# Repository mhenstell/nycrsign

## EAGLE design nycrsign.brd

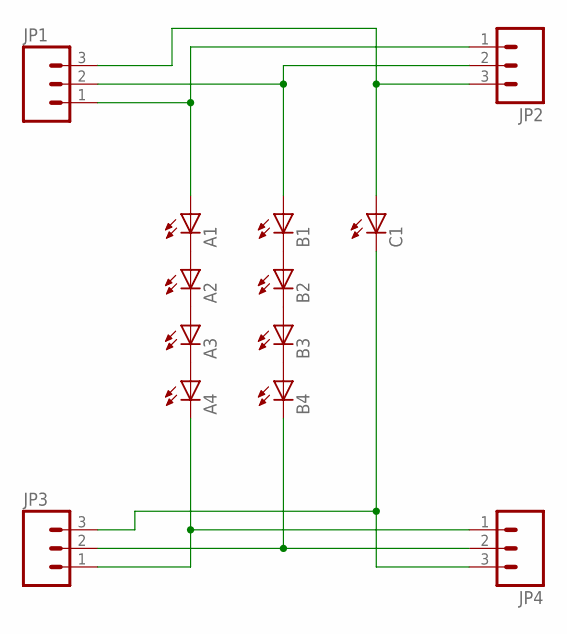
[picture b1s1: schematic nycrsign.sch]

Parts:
A1, A2, A3, A4: LED5MM
B1, B2, B3, B4: LED5MM
C1: LED5MM
JP1, JP2, JP3, JP4: M03LONGPADS; 1X03_LONGPADS

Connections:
A4: A4.K (C), JP3.1, JP4.1
unnamed: A1.K (C), A2.A
unnamed: A2.K (C), A3.A
unnamed: A3.K (C), A4.A
unnamed: B1.K (C), B2.A
unnamed: B2.K (C), B3.A
unnamed: B3.K (C), B4.A
unnamed: A1.A, JP1.1, JP2.1
unnamed: B1.A, JP1.2, JP2.2
unnamed: C1.A, JP1.3, JP2.3
unnamed: B4.K (C), JP3.2, JP4.2
unnamed: C1.K (C), JP3.3, JP4.3

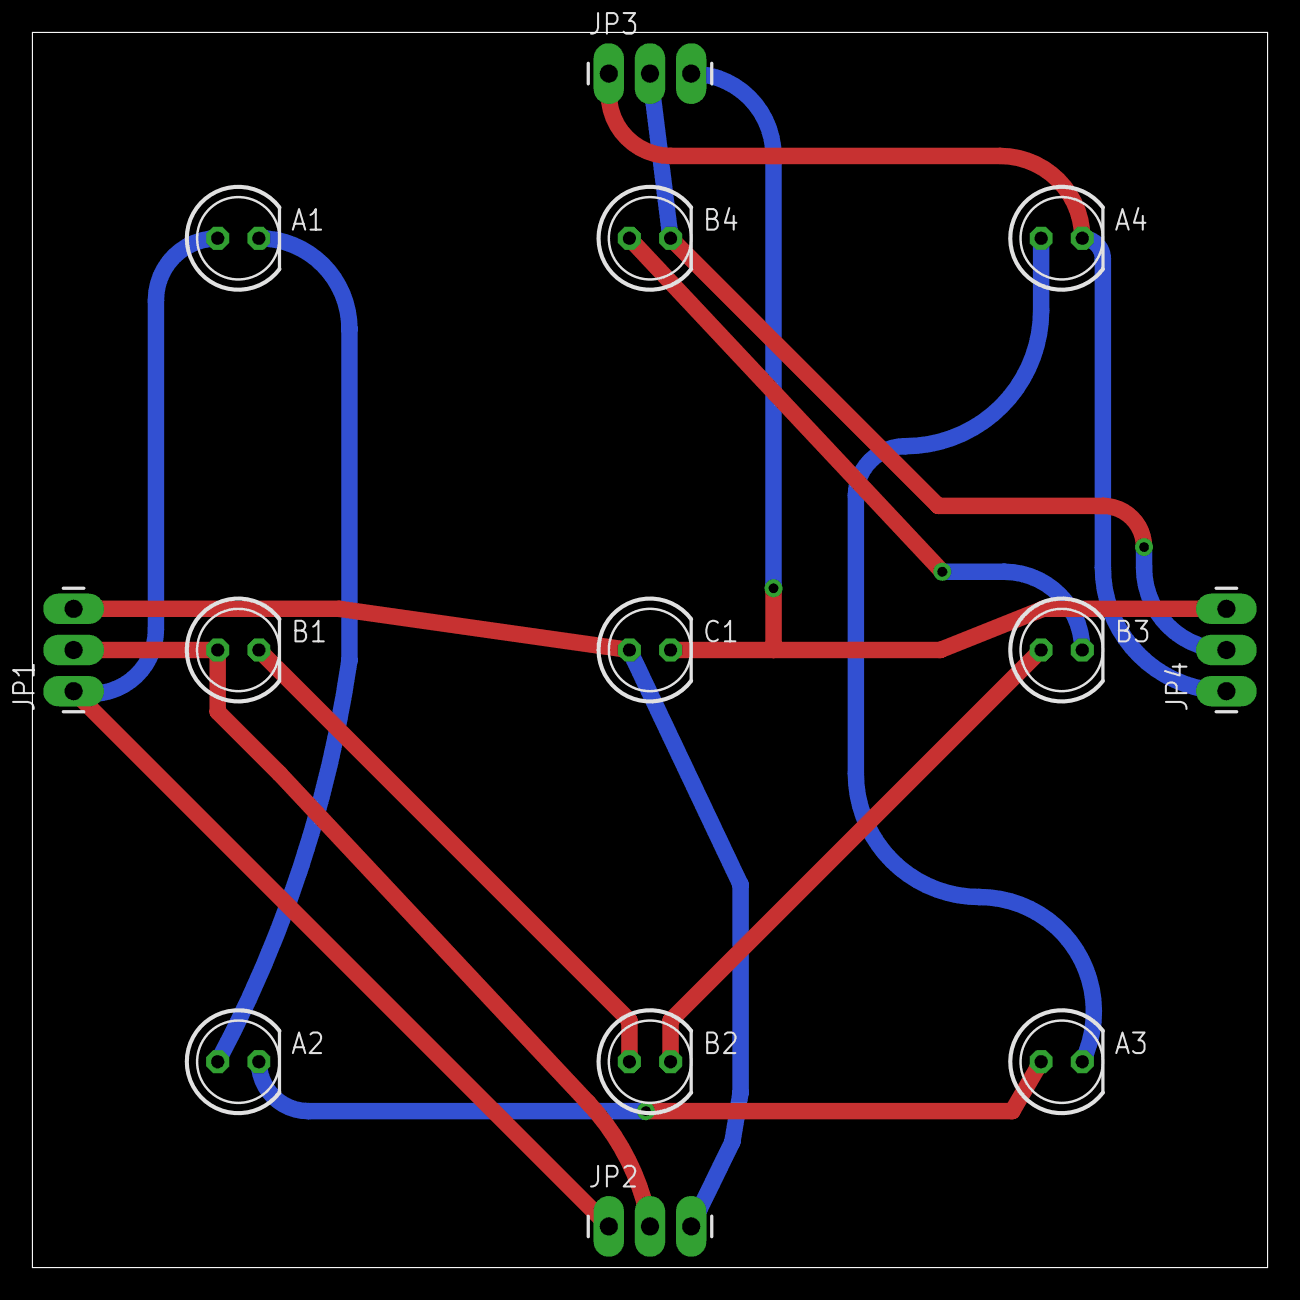
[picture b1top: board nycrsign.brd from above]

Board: 2 copper layers, 76.2 x 76.2 mm, 13 parts (0 on the bottom side), 12 nets.

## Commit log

2012-03-22 first
2012-03-22 fixed username?
2012-03-23 gitignore
2012-03-23 routed board
2012-03-23 working simulator
2012-03-23 fixed README
2012-03-23 started adding letters class
2012-03-25 deleting eagle 6 boards
